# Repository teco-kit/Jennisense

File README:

A modularized open hardware, sensor drivers based on contiki for the JN51xx µController. A detailed description and how-to can be found in the wiki (see link below).
http://github.com/teco-kit/Jennisense/wiki

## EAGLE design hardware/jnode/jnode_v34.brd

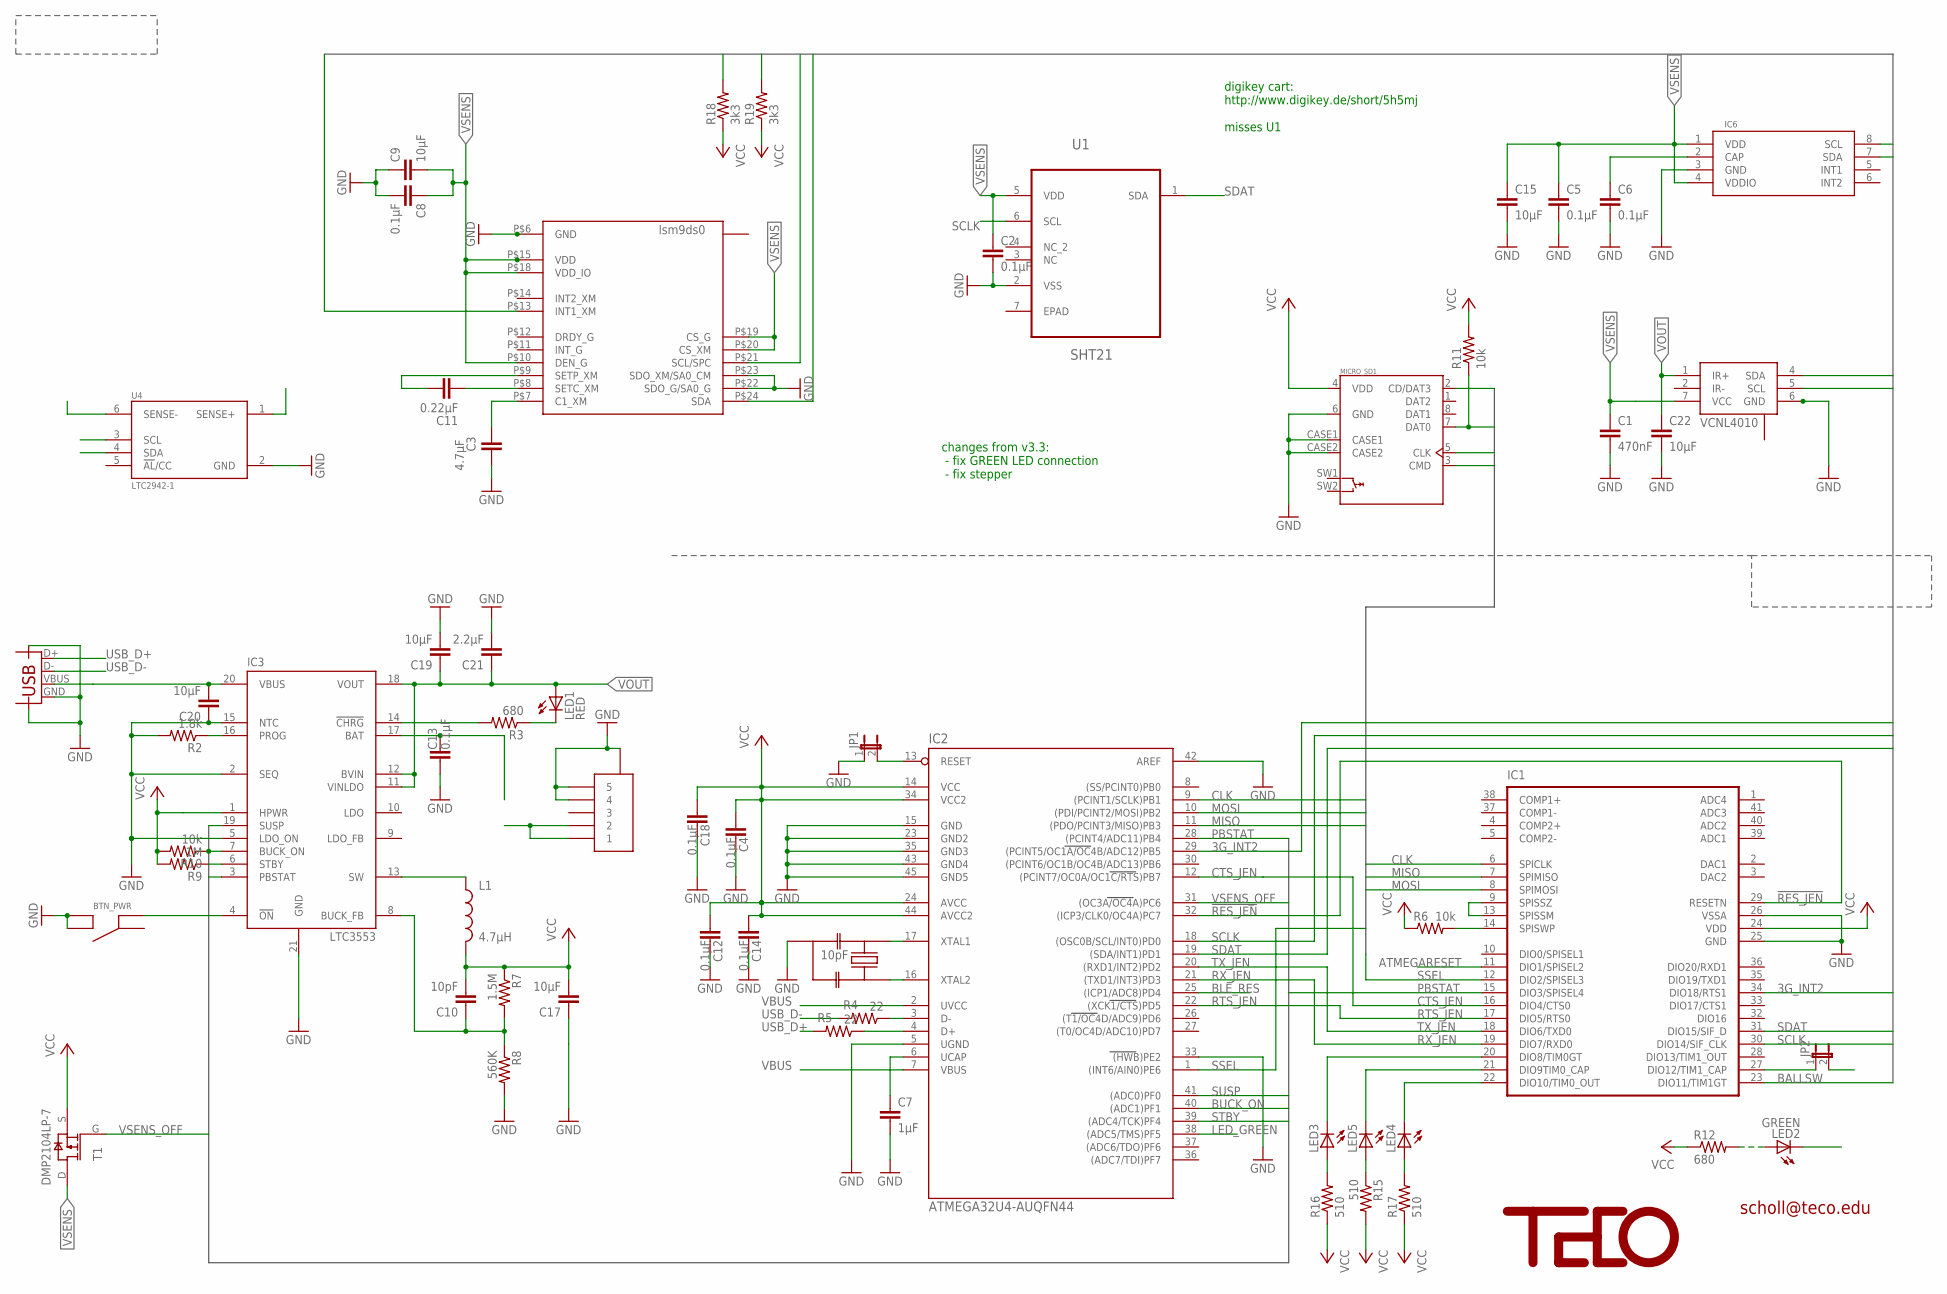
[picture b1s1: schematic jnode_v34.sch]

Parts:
BTN_PWR: TACTILE_SWITCH; EVQ-PUK02K; DIGIKEY P10852SCT-ND
C1: 470nF; 0402-CAP; DIGIKEY 587-1230-1-ND
C2, C4, C5, C6, C8, C12, C13, C14, C18: 0.1µF; 0402-CAP; DIGIKEY 490-1318-1-ND
C3: 4.7µF; 0402-CAP; DIGIKEY 1276-1056-1-ND
C7: 1µF; 0402-CAP; DIGIKEY 490-1320-1-ND
C9, C15, C17, C19, C20, C22: 10µF; 0603-CAP; DIGIKEY 445-7454-1-ND
C10: 10pF; 0402-CAP; DIGIKEY 311-1014-1-ND
C11: 0.22µF; 0402-CAP; DIGIKEY 399-4886-1-ND
C21: 2.2µF; 0402-CAP; DIGIKEY 445-7396-1-ND
IC1: JENNIC_JN51XXSMDTH; JN5148_SMDTH; DIGIKEY 616-1045-1-ND
IC2: ATMEGA32U4-AUQFN44; QFN44; DIGIKEY ATMEGA32U4-MU-ND
IC3: LTC3553; QFN20; DIGIKEY LTC3553EUD#PBF-ND
IC6: MPL3115A2; LGA8
JP1: JUMPER-2SMD-NO; SJ_2S-NO
JP2: JUMPER-2SMD-NC; SJ_2S
L1: 4.7µH; MLP2012; DIGIKEY 445-6366-1-ND
LED1: RED; CHIP-LED0402; DIGIKEY 754-1128-1-ND
LED2: GREEN; CHIP-LED0402; DIGIKEY 754-1127-1-ND
LED3, LED4, LED5: LEDGL100MD1MP1; GL100MD1MP1
MICRO_SD1: MOLEX_47309-2651NEW; MOLEX_47309-2651; DIGIKEY WM3974CT-ND
R2: 1.8k; 0402-RES; DIGIKEY 311-1.8KJRCT-ND
R3, R12: 680; 0402-RES; DIGIKEY RHM680CDCT-ND
R4, R5: 22; 0402-RES; DIGIKEY 311-22JRCT-ND
R6, R10, R11: 10k; 0402-RES; DIGIKEY RHM10.0KCDCT-ND
R7: 1.5M; 0402-RES; DIGIKEY 311-1.5MJRCT-ND
R8: 560K; 0402-RES; DIGIKEY P560KLCT-ND
R9: 1M; 0402-RES; DIGIKEY 311-1.00MLRCT-ND
R15, R16, R17: 510; 0402-RES
R18, R19: 3k3; 0402-RES; DIGIKEY 1276-3460-1-ND
T1: DMP2104LP-7; DFN1411-3; DIGIKEY DMP2104LPDICT-ND
U1: SHT21; DFN300X300X110-7N
U2: LSM9D; LGA4X4
U3: SFV5R; DIGIKEY 609-4330-1-ND
U4: LTC2942-1; DFN6; DIGIKEY LTC2942IDCB-1#TRMPBFCT-ND
U6: RESONATORPRQC-S; PRQC; DIGIKEY 478-5420-1-ND
U$9: TECO-LOGO
VCNL4010: VCNL4000; VNCL4000; DIGIKEY VCNL4010-GS08CT-ND
X1: USBMICROB-XT; USB-MICROB-XT; DIGIKEY H11635CT-ND

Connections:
3G_INT2: IC1.34 (DIO18/RTS1), IC2.29 ((PCINT5/OC1A/OC4B/ADC12)PB5), U2.P$13 (INT1_XM)
!RES_JEN: IC1.29 (RESETN), IC2.32 ((ICP3/CLK0/OC4A)PC7)
ATMEGARESET: IC1.11 (DIO1/SPISEL2), IC2.13 (RESET), JP1.2
BALLSW: IC1.23 (DIO11/TIM1GT)
BLE_RES: IC2.25 ((ICP1/ADC8)PD4)
BUCK_FB: C10.1, IC3.8 (BUCK_FB), R7.2, R8.1
BUCK_ON: IC2.40 ((ADC1)PF1), IC3.7 (BUCK_ON), R10.1
CLK: IC1.6 (SPICLK), IC2.9 ((PCINT1/SCLK)PB1), MICRO_SD1.5 (CLK)
CTS_JEN: IC1.16 (DIO4/CTS0), IC2.12 ((PCINT7/OC0A/OC1C/RTS)PB7)
GND: BTN_PWR.2 (B), BTN_PWR.4 (B), C1.2, C2.2, C3.2, C4.1, C5.2, C6.2, C7.2, C8.2, C9.1, C12.1, C13.2, C14.1, C15.2, C17.1, C18.1, C19.2, C20.1, C21.2, C22.2, IC1.25 (GND), IC1.26 (VSSA), IC2.5 (UGND), IC2.15 (GND), IC2.23 (GND2), IC2.33 ((HWB)PE2), IC2.35 (GND3), IC2.42 (AREF), IC2.43 (GND4), IC2.45 (GND5), IC3.2 (SEQ), IC3.5 (LDO_ON), IC3.15 (NTC), IC3.21 (GND), IC6.3 (GND), JP1.1, MICRO_SD1.6 (GND), MICRO_SD1.CASE1, MICRO_SD1.CASE2, R2.2, R8.2, U1.2 (VSS), U2.P$5 (GND), U2.P$6 (GND), U2.P$22 (SDO_G/SA0_G), U2.P$23 (SDO_XM/SA0_CM), U3.P$4 (4), U3.P$5 (5), U3.P$6, U3.P$7, U4.2 (GND), U6.GND, VCNL4010.6 (GND), VCNL4010.12 (GND), X1.GND, X1.GND@2 (CASE), X1.GND@3 (CASE)
LED_GREEN: IC2.38 ((ADC5/TMS)PF5), LED2.P$2 (C)
MISO: IC1.7 (SPIMISO), IC2.11 ((PDO/PCINT3/MISO)PB3), MICRO_SD1.7 (DAT0), R11.1
MOSI: IC1.8 (SPIMOSI), IC2.10 ((PDI/PCINT2/MOSI)PB2), MICRO_SD1.3 (CMD)
unnamed: IC2.3 (D-), R4.1
unnamed: C3.1, U2.P$7 (C1_XM)
unnamed: IC2.4 (D+), R5.1
unnamed: C7.1, IC2.6 (UCAP)
unnamed: IC3.16 (PROG), R2.1
unnamed: VCNL4010.2 (IR-), VCNL4010.3 (IR-)
unnamed: C11.2, U2.P$8 (SETC_XM)
unnamed: C11.1, U2.P$9 (SETP_XM)
unnamed: BTN_PWR.3 (A), IC3.4 (!ON)
unnamed: C6.1, IC6.2 (CAP)
unnamed: LED1.P$2 (C), R3.1
unnamed: IC3.14 (!CHRG), R3.2
unnamed: IC1.9 (SPISSZ), IC1.13 (SPISSM)
unnamed: IC1.14 (SPISWP), R6.2
unnamed: IC2.17 (XTAL1), U6.2
unnamed: IC2.16 (XTAL2), U6.1
unnamed: IC1.27 (DIO12/TIM1_CAP), JP2.1
unnamed: LED2.P$1 (A), R12.2
unnamed: IC1.21 (DIO9TIM0_CAP), LED5.2 (C)
unnamed: IC1.20 (DIO8/TIM0GT), LED3.2 (C)
unnamed: LED3.1 (A), R16.2
unnamed: LED5.1 (A), R15.1
unnamed: IC1.22 (DIO10/TIM0_OUT), LED4.2 (C)
unnamed: LED4.1 (A), R17.2
PBSTAT: IC1.15 (DIO3/SPISEL4), IC2.28 ((PCINT4/ADC11)PB4), IC3.3 (PBSTAT)
RTS_JEN: IC1.17 (DIO5/RTS0), IC2.22 ((XCK1/CTS)PD5)
RX_JEN: IC1.19 (DIO7/RXD0), IC2.21 ((TXD1/INT3)PD3)
SCLK: IC1.30 (DIO14/SIF_CLK), IC2.18 ((OSC0B/SCL/INT0)PD0), IC6.8 (SCL), R19.2, U1.6 (SCL), U2.P$21 (SCL/SPC), U4.3 (SCL), VCNL4010.5 (SCL)
SDAT: IC1.31 (DIO15/SIF_D), IC2.19 ((SDA/INT1)PD1), IC6.7 (SDA), R18.2, U1.1 (SDA), U2.P$24 (SDA), U4.4 (SDA), VCNL4010.4 (SDA)
SENSE+: C13.1, IC3.17 (BAT), U4.1 (SENSE+)
SENSE-: JP2.2, U3.P$1 (1), U3.P$2 (2), U4.6 (SENSE-)
SSEL: IC1.12 (DIO2/SPISEL3), IC2.1 ((INT6/AIN0)PE6), MICRO_SD1.2 (CD/DAT3)
STBY: IC2.39 ((ADC4/TCK)PF4), IC3.6 (STBY), R9.1
SUSP: IC2.41 ((ADC0)PF0), IC3.19 (SUSP)
SW: IC3.13 (SW), L1.P$1 (1)
TX_JEN: IC1.18 (DIO6/TXD0), IC2.20 ((RXD1/INT2)PD2)
USB_D+: R5.2, X1.D+
USB_D-: R4.2, X1.D-
VBUS: C20.2, IC2.2 (UVCC), IC2.7 (VBUS), IC3.20 (VBUS), X1.VBUS
VCC: C4.2, C10.2, C12.2, C14.2, C17.2, C18.2, IC1.24 (VDD), IC2.14 (VCC), IC2.24 (AVCC), IC2.34 (VCC2), IC2.44 (AVCC2), IC3.1 (HPWR), L1.P$2 (2), MICRO_SD1.4 (VDD), R6.1, R7.1, R9.2, R10.2, R11.2, R12.1, R15.2, R16.1, R17.1, R18.1, R19.1, T1.S
VOUT: C19.1, C21.1, C22.1, IC3.11 (VINLDO), IC3.12 (BVIN), IC3.18 (VOUT), LED1.P$1 (A), VCNL4010.1 (IR+)
VSENS: C1.1, C2.1, C5.1, C8.1, C9.2, C15.1, IC6.1 (VDD), IC6.4 (VDDIO), T1.D, U1.5 (VDD), U2.P$10 (DEN_G), U2.P$15 (VDD), U2.P$16 (VDD), U2.P$17 (VDD), U2.P$18 (VDD_IO), U2.P$19 (CS_G), U2.P$20 (CS_XM), VCNL4010.7 (VCC)
VSENS_OFF: IC2.31 ((OC3A/OC4A)PC6), T1.G

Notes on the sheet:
scholl@teco.edu
10pF
digikey cart: http://www.digikey.de/short/5h5mj misses U1
changes from v3.3: - fix GREEN LED connection - fix stepper

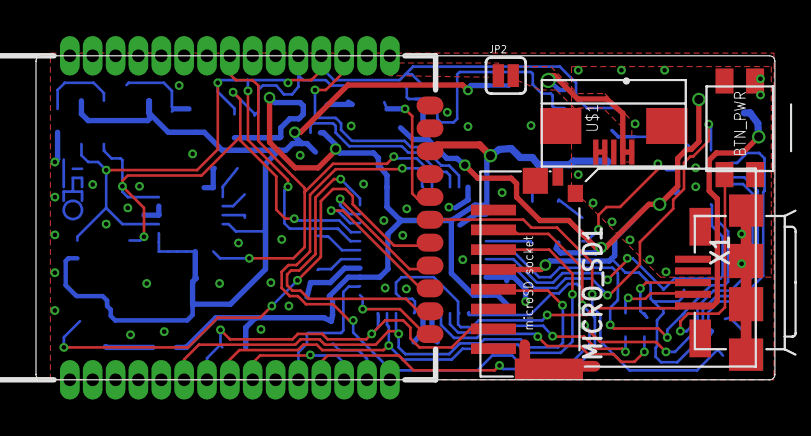
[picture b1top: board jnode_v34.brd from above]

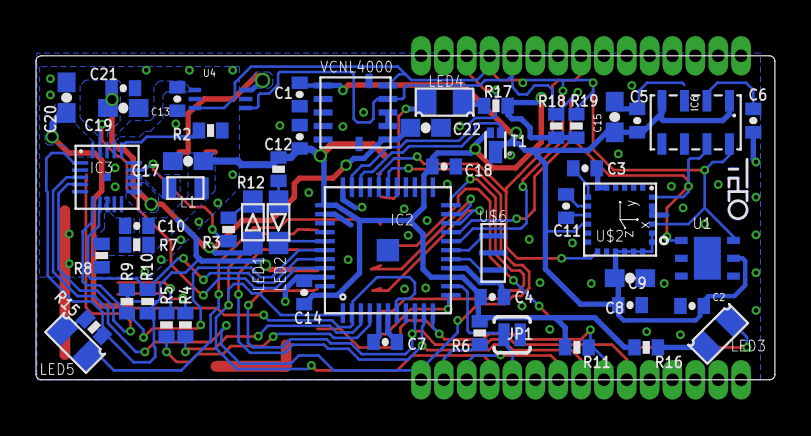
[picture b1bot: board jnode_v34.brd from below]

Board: 2 copper layers, 41.0 x 18.0 mm, 60 parts (54 on the bottom side), 54 nets.

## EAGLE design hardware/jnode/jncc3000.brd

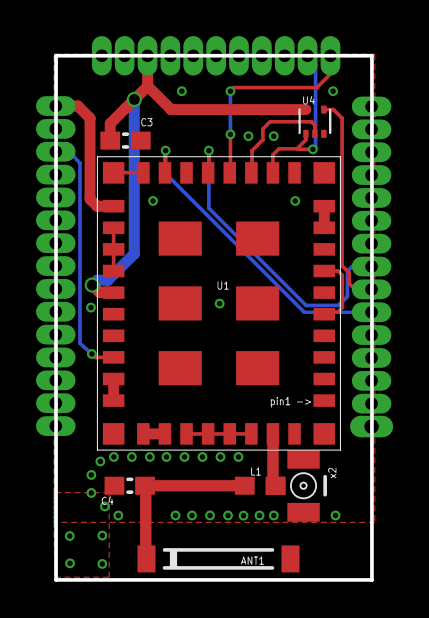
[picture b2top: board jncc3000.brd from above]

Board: 2 copper layers, 17.6 x 29.1 mm, 8 parts (0 on the bottom side), 15 nets.

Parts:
ANT1: AT8010
C3: 100nF; C0603
C4: 0.8pF; C0603
L1: 3.3nH; 0603
U1: CC3000
U4: SOT-553
U$2: JN5139_TH
X2: IPEX-20279-001E

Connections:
+3V3: C3.1, U1.VIO_HOST, U4.VCC, U$2.P$24
GND: C3.2, C4.2, U1.EXT_32K, U1.GND@1, U1.GND@9, U1.GND@10, U1.GND@11, U1.GND@16, U1.GND@18, U1.GND@20, U1.GND@22, U1.GND@25, U1.GND@31, U1.GND@32, U1.GND@33, U1.GND@34, U1.GND@36, U1.GND@37, U1.GND@38, U1.GND@39, U1.GND@40, U1.GND@41, U1.GND@42, U1.GND@43, U1.GND@44, U1.GND@45, U1.GND@46, U4.GND, U$2.P$25, X2.2@1, X2.2@2
unnamed: L1.2, U1.RF_ANT, X2.1
unnamed: ANT1.SIG, C4.1, L1.1
unnamed: U1.SCL_CC3000, U1.SCL_EEPROM
unnamed: U1.WL_EN1, U1.WL_EN2
unnamed: U1.SDA_CC3000, U1.SDA_EEPROM
SPI_DOUT: U1.SPI_DOUT, U4.IN
SPI_MISO: U4.OUT, U$2.P$7
SPI_MOSI: U1.SPI_DIN, U$2.P$8
SPI_SCK: U1.SPI_CLK, U$2.P$6
VBAT: U1.VBAT_IN, U$2.P$27
WIFI_CS: U1.SPI_CS, U4./OE, U$2.P$17
WIFI_EN: U1.VBAT_SW_EN, U$2.P$29
WIFI_INT: U1.SPI_IRQ, U$2.P$16

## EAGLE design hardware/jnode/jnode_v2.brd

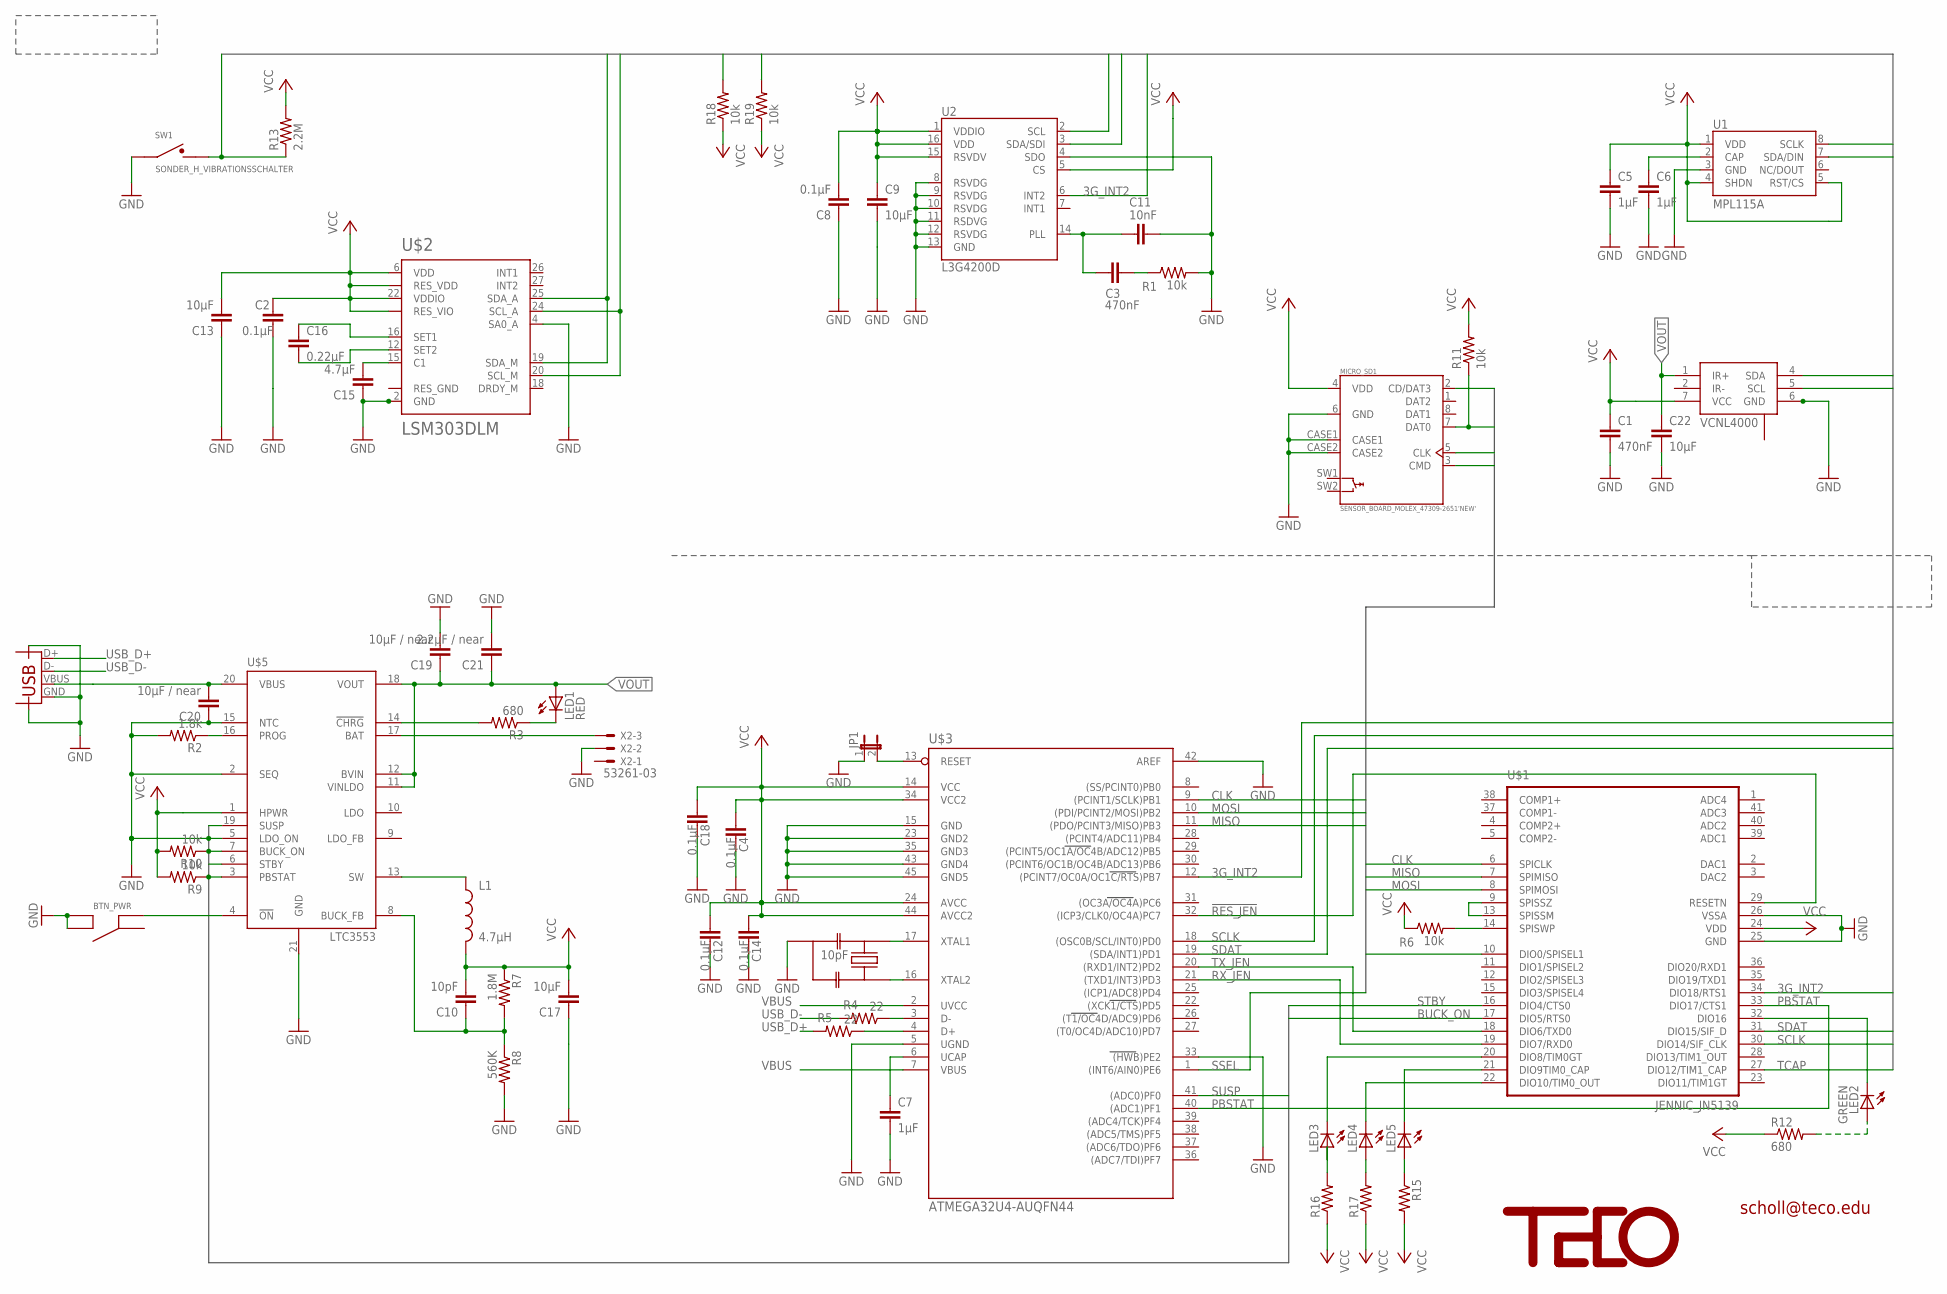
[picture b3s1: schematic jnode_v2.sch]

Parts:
BTN_PWR: TACTILE_SWITCH; EVQ-PUK02K
C1, C3: 470nF; 0402-CAP
C2, C4, C8, C12, C14, C18: 0.1µF; 0402-CAP
C5, C6, C7: 1µF; 0402-CAP
C9, C13, C17, C22: 10µF; 0603-CAP
C10: 10pF; 0402-CAP
C11: 10nF; 0402-CAP
C15: 4.7µF; 0402-CAP
C16: 0.22µF; 0402-CAP
C19, C20: 10µF / near; 0603-CAP
C21: 2.2µF / near; 0402-CAP
JP1: JUMPER-2SMD-NO; SJ_2S-NO
L1: 4.7µH; MLP2012
LED1: RED; CHIP-LED0402
LED2: GREEN; CHIP-LED0402
LED3, LED4, LED5: LEDGL100MD1MP1; GL100MD1MP1
MICRO_SD1: SENSOR_BOARD_MOLEX_47309-2651'NEW'; SENSOR_BOARD_MOLEX_47309-2651
R1, R6, R9, R10, R11, R18, R19: 10k; 0402-RES
R2: 1.8k; 0402-RES
R3, R12: 680; 0402-RES
R4, R5: 22; 0402-RES
R7: 1.8M; 0402-RES
R8: 560K; 0402-RES
R13: 2.2M; 0805
R15, R16, R17: RESISTOR0402-RES; 0402-RES
SW1: SONDER_H_VIBRATIONSSCHALTER; SONDER_H_VIBSCHALTER
U1: MPL115A; LGA8
U2: L3G4200D; LGA16-4X4
U$1: JENNIC_JN5139; JN5148_SMDTH
U$2: LSM303DLM; LGA28
U$3: ATMEGA32U4-AUQFN44; QFN44
U$5: LTC3553; QFN20
U$6: RESONATORPRQC-S; PRQC
U$9: TECO-LOGO
VCNL4000: VCNL4000; VNCL4000
X1: USB-MICROB
X2: 53261-03

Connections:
3G_INT2: U2.6 (INT2), U$1.34 (DIO18/RTS1), U$3.12 ((PCINT7/OC0A/OC1C/RTS)PB7)
!RES_JEN: U$1.29 (RESETN), U$3.32 ((ICP3/CLK0/OC4A)PC7)
BUCK_FB: C10.1, R7.2, R8.1, U$5.8 (BUCK_FB)
BUCK_ON: R10.1, U$1.17 (DIO5/RTS0), U$5.7 (BUCK_ON)
CLK: MICRO_SD1.5 (CLK), U$1.6 (SPICLK), U$3.9 ((PCINT1/SCLK)PB1)
GND: BTN_PWR.2 (B), BTN_PWR.4 (B), C1.2, C2.2, C4.1, C5.2, C6.2, C7.2, C8.1, C9.2, C11.1, C12.1, C13.1, C14.1, C15.1, C17.1, C18.1, C19.2, C20.1, C21.2, C22.2, JP1.1, MICRO_SD1.6 (GND), MICRO_SD1.CASE1, MICRO_SD1.CASE2, R1.2, R2.2, R8.2, SW1.1, U1.3 (GND), U2.4 (SDO), U2.8 (RSVDG), U2.9 (RSVDG), U2.10 (RSVDG), U2.11 (RSDVG), U2.12 (RSVDG), U2.13 (GND), U$1.25 (GND), U$1.26 (VSSA), U$2.2 (GND), U$2.4 (SA0_A), U$3.5 (UGND), U$3.15 (GND), U$3.23 (GND2), U$3.33 ((HWB)PE2), U$3.35 (GND3), U$3.42 (AREF), U$3.43 (GND4), U$3.45 (GND5), U$5.2 (SEQ), U$5.5 (LDO_ON), U$5.15 (NTC), U$5.21 (GND), U$6.GND, VCNL4000.6 (GND), VCNL4000.12 (GND), X1.GND, X1.GND@2 (CASE), X1.GND@3 (CASE), X2.2
LEDRED: LED2.P$2 (C), U$1.32 (DIO16)
MISO: MICRO_SD1.7 (DAT0), R11.1, U$1.7 (SPIMISO), U$3.11 ((PDO/PCINT3/MISO)PB3)
MOSI: MICRO_SD1.3 (CMD), U$1.8 (SPIMOSI), U$3.10 ((PDI/PCINT2/MOSI)PB2)
unnamed: R4.1, U$3.3 (D-)
unnamed: C16.1, U$2.16 (SET1)
unnamed: R5.1, U$3.4 (D+)
unnamed: C7.1, U$3.6 (UCAP)
unnamed: R2.1, U$5.16 (PROG)
unnamed: VCNL4000.2 (IR-), VCNL4000.3 (IR-)
unnamed: C16.2, U$2.12 (SET2)
unnamed: BTN_PWR.3 (A), U$5.4 (!ON)
unnamed: C6.1, U1.2 (CAP)
unnamed: LED1.P$2 (C), R3.1
unnamed: R3.2, U$5.14 (!CHRG)
unnamed: U$1.9 (SPISSZ), U$1.13 (SPISSM)
unnamed: R6.2, U$1.14 (SPISWP)
unnamed: U$3.17 (XTAL1), U$6.2
unnamed: U$3.16 (XTAL2), U$6.1
unnamed: C15.2, U$2.15 (C1)
unnamed: C3.1, C11.2, U2.14 (PLL)
unnamed: C3.2, R1.1
unnamed: LED2.P$1 (A), R12.2
unnamed: LED5.2 (C), U$1.21 (DIO9TIM0_CAP)
unnamed: LED3.2 (C), U$1.20 (DIO8/TIM0GT)
unnamed: LED3.1 (A), R16.2
unnamed: LED5.1 (A), R15.1
unnamed: LED4.2 (C), U$1.22 (DIO10/TIM0_OUT)
unnamed: LED4.1 (A), R17.2
PBSTAT: R9.1, U$1.33 (DIO17/CTS1), U$3.40 ((ADC1)PF1), U$5.3 (PBSTAT)
RX_JEN: U$1.19 (DIO7/RXD0), U$3.21 ((TXD1/INT3)PD3)
SCLK: R19.2, U1.8 (SCLK), U2.2 (SCL), U$1.30 (DIO14/SIF_CLK), U$2.20 (SCL_M), U$2.24 (SCL_A), U$3.18 ((OSC0B/SCL/INT0)PD0), VCNL4000.5 (SCL)
SDAT: R18.2, U1.7 (SDA/DIN), U2.3 (SDA/SDI), U$1.31 (DIO15/SIF_D), U$2.19 (SDA_M), U$2.25 (SDA_A), U$3.19 ((SDA/INT1)PD1), VCNL4000.4 (SDA)
SHWO: JP1.2, U$3.13 (RESET)
SSEL: MICRO_SD1.2 (CD/DAT3), U$1.10 (DIO0/SPISEL1), U$3.1 ((INT6/AIN0)PE6)
STBY: U$1.16 (DIO4/CTS0), U$5.6 (STBY)
SUSP: U$3.41 ((ADC0)PF0), U$5.19 (SUSP)
SW: L1.P$1 (1), U$5.13 (SW)
TCAP: R13.1, SW1.2, U$1.27 (DIO12/TIM1_CAP)
TX_JEN: U$1.18 (DIO6/TXD0), U$3.20 ((RXD1/INT2)PD2)
USB_D+: R5.2, X1.D+
USB_D-: R4.2, X1.D-
VBATT: U$5.17 (BAT), X2.3
VBUS: C20.2, U$3.2 (UVCC), U$3.7 (VBUS), U$5.20 (VBUS), X1.VBUS
VCC: C1.1, C2.1, C4.2, C5.1, C8.2, C9.1, C10.2, C12.2, C13.2, C14.2, C17.2, C18.2, L1.P$2 (2), MICRO_SD1.4 (VDD), R6.1, R7.1, R9.2, R10.2, R11.2, R12.1, R13.2, R15.2, R16.1, R17.1, R18.1, R19.1, U1.1 (VDD), U1.4 (SHDN), U1.5 (RST/CS), U2.1 (VDDIO), U2.5 (CS), U2.15 (RSVDV), U2.16 (VDD), U$1.24 (VDD), U$2.6 (VDD), U$2.7 (RES_VDD), U$2.22 (VDDIO), U$2.23 (RES_VIO), U$3.14 (VCC), U$3.24 (AVCC), U$3.34 (VCC2), U$3.44 (AVCC2), U$5.1 (HPWR), VCNL4000.7 (VCC)
VOUT: C19.1, C21.1, C22.1, LED1.P$1 (A), U$5.11 (VINLDO), U$5.12 (BVIN), U$5.18 (VOUT), VCNL4000.1 (IR+)

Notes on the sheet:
scholl@teco.edu
10pF

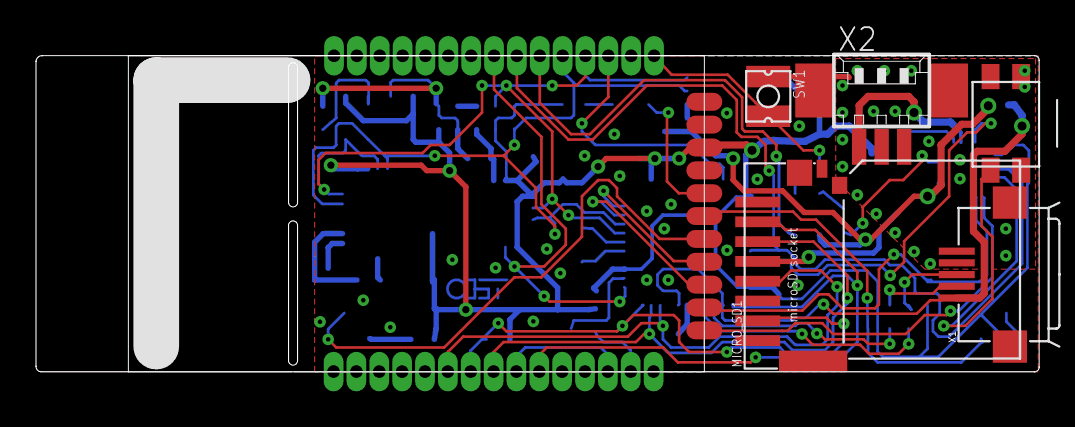
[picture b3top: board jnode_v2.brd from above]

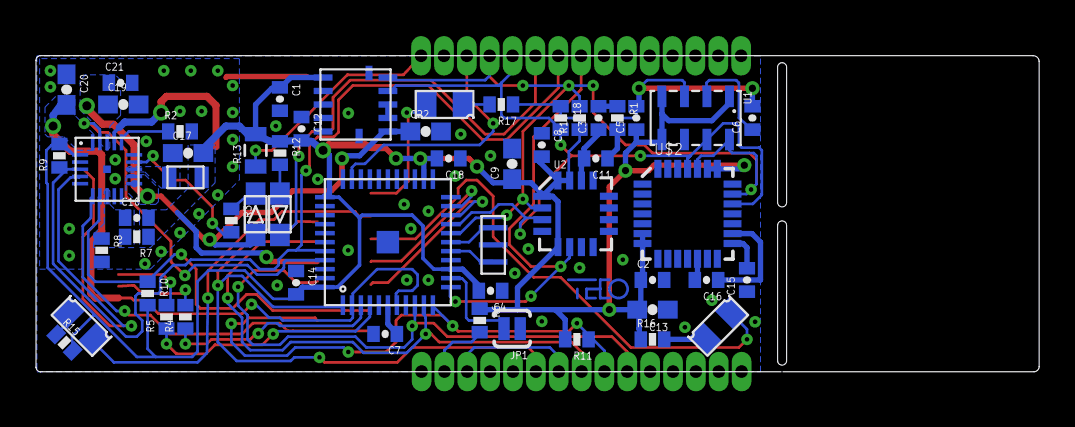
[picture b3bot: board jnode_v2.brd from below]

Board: 2 copper layers, 55.7 x 17.6 mm, 61 parts (55 on the bottom side), 51 nets.

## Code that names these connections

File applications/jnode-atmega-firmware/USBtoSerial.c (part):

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#define RTSEN 0
#define CTSEN 1

#define JEN_RESETN  _BV(7) /* PC7 */
#define JEN_SPIMISO _BV(3) /* PB3 */
#define JEN_SPIMOSI _BV(2) /* PB2 */
#define JEN_CLOCK   _BV(1) /* PB1 */
#define JEN_SPISS   _BV(6) /* PE6 */

#define PWR_BUCKON  _BV(1) /* PF1, on by default */
#define PWR_STBY    _BV(4) /* PF4, pull low! */
#define PWR_BUTTON  _BV(4) /* PB4, input pin */
#define PWR_SENSORS _BV(6) /* PC6, on by default, toggle for reset */

/** Circular buffer to hold data from the host before it is sent to the device via the serial port. */
static RingBuffer_t USBtoUSART_Buffer;
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  MCUSR &= ~(1 << WDRF);
  wdt_disable();

  /* disable JTAG since we use the pins for I/O, e.g. the STBY pin */
  JTAG_DISABLE();

  /* disable clock division, run on 16MHz */
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
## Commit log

2011-08-18 * Initial commit of Jennisense combining specific jennic example applications and the contiki OS port.
2011-08-18 * Added basic readme file to Jennisense
2011-08-18 * Adapted makefile to changed directory structure for application examples.
2011-08-21 * Added jnsub and jndis hardware schematics.
2011-08-23 * Added hello-world-leds example to applications.
2011-08-23 * Added ethbridge to applications and branched ethbridge and contiki to stable.
2011-08-23 * Updated commit point of submodule ethbridge in order to update to latest Makefile changes.
2011-10-03 jnusb v30 hardware
    Mickael Bosch contributed a minimal version of the jennic usb board. Leds (not
    used by the firmware), push-buttons and programming header have been removed.
    The programming connector was hardly used and for reprogramming the pads have to
    be directly connected to a serial converter now, which needs to be done only
    once.
    (this design is un-tested)
2011-10-05 jnode hardware
    Jennic with atmega usb connector, a number of sensors
    (compass,gyro,acc,temp,barometer,ambient light,ir distance,ir leds).
    Design is yet untested.
2011-10-07 missing pcb link on jnusb
    between SPISSZ and SPISSM
2011-10-07 fixed a missing link jnusb
2012-02-02 jnode quirks
    fix power path for sdcard init without turning off other components
    for atmega bootloader operation:
    HWB hardwired to GND
    jumper on RESET line
    to get into bootloader short the reset line
2012-02-02 add very basic imu-serial example for jnode hw
2012-03-09 add atmega32u4 serial firmware
    upload to jnode by toggling the reset pad on the board and uploading with
    dfu-programmer
2012-03-09 add imu-serial demo
2012-03-19 update jnode schematic and board
2012-03-20 fix on the STDBY and BUCK_ON line
2012-03-21 fix value of I2C pull-ups
2012-03-30 * Added the Jbee board. The a jennic board compatible to the popular xbee footprint.
2012-04-29 * moved submodule to latest version of contiki for jennic
2012-06-25 add button sensor example
    shows how to listen and react on pushbutton events
2012-06-25 also check that event is really from button
2012-07-31 Add the basic jnode-lufa firmware
2012-08-01 fix hello world example
    Thanks Ant Skelton
2012-10-19 * Updated to more recent version of contiki
2012-11-15 add jnode_v3 layout and v31
    v31 replacess the battery connector to one compatible with the Ipod Video 5g
    battery, which is almost the same size as the jNode.
2012-11-16 lufa update and default baudrate
    switch to newest LUFA.
    configure the default baudrate to 1M, so no caring on PC side is neccesary to
    set the one for talking to the jennic module.
2012-11-16 simplify imu-serial and atmega firmware
2012-11-16 add ahrs example
2013-01-14 added two basic apllication to receive imu data periodically via IPv6/concom
2013-02-07 * clarified button example to show change of button state
2013-02-07 * updated submodule contiki to latest release (patches for serial)
2013-02-22 added envboard application
2013-05-27 * added some python code to parse output from jenv and jn gw code !!experimental!!
2013-05-27 * changed version of contiki submodule
2013-05-28 * gateway code currently not correctly working (coordinator function obviously defective) * remainder works
2013-05-28 * changes
2013-06-05 * fixed gw. removed debugging output.
2013-06-05 * added working gateway hex. at this time no panid. doesnt work.
2014-04-06 cc3000 wifi board for jnode
2014-06-05 add v33 jnode and cc3000 adapter board
2014-07-05 add pre-test jnode_v34
2014-08-19 update jnode

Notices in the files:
applications/jnode-atmega-firmware/USBtoSerial.c:
Copyright (C) Dean Camera, 2012.
Copyright 2012  Dean Camera (dean [at] fourwalledcubicle [dot] com)
parts and their libraries:
SparkFun-Passives: Licensing: CC v3.0 Share-Alike You are welcome to use this library for commercial purposes.
SparkFun-Passives: Licensing: Creative Commons ShareAlike 4.0 International - https://creativecommons.org/licenses/by-sa/4.0
